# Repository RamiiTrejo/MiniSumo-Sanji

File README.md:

# MiniSumo-Sanji
Minisumo

 ## PLaca de Sanji
  Sanji contará con una placa hecha medida la cual puede ser alimentada con baterias de 2s-3s (LiPo), Con un microcontrolador ESP32 Embebido posee la capacidad de llevar 7 sensores, 5 de distancia y 2 de piso, con Divisores de tension en caso de trabajar con 5v, posee drivers TA6586 los cuales pueden llegar a soportar 5A de corriente pico por cada motor, tiene la opcion de agregar Pantalla Oled de 0.91 de Preferencia, ServoMotor para utilizarlo con Banderas, y Modulo de Inicio IR de Arsumo, 2 Botones de Manejo, 2 para poder cargar Programas al ESP32, y 3 Leds indicadores en caso de no querer utilizar un Display

<div align="center">
<br>
 <strong>FRONT VIEW</strong>
</div> 

<div align="center">
 <br>
 <strong>BACK VIEW</strong>
</div> 

 # 3D Sanji

cómo se aprecia en kas imágenes, Sanji Llevara de momento 4 sensores JS40F De arsumo, también poseerá 1 par de ruedas JS2622, 2 sensores de línea QRE1113, y de momento par de Motores pololu N20 de 500RPM

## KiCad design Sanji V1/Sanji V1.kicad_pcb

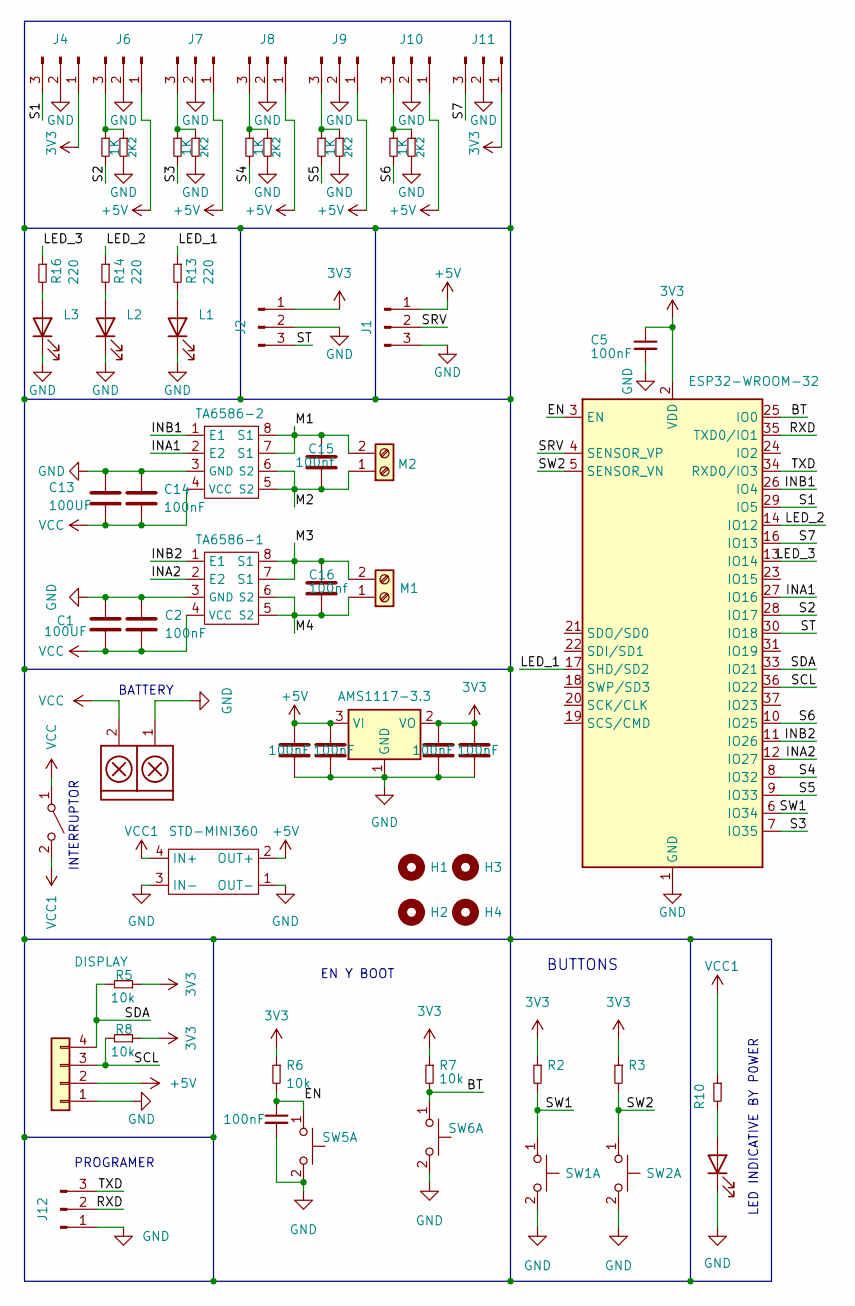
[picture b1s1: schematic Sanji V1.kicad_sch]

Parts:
Alimentacion1: TB_1X2; AMASS_XT30U-M_1x02_P5.0mm_Vertical
C1, C13: 100UF; CP_EIA-7343-20_Kemet-V
C2, C3, C4, C5, C6, C7, C8, C14: 100nF; C_0805_2012Metric_Pad1.18x1.45mm_HandSolder
C15, C16: 100nf; C_0805_2012Metric_Pad1.18x1.45mm_HandSolder
D2: LED; LED_0805_2012Metric_Pad1.15x1.40mm_HandSolder
H1, H2, H3, H4: MountingHole; MountingHole_3mm
J1, J2, J12: Conn_01x03_Pin; PinHeader_1x03_P2.54mm_Vertical
J3: DISPLAY; PinSocket_1x04_P2.54mm_Vertical
J4, J6, J7, J8, J9, J10, J11: Conn_01x03_Pin; PinHeader_1x03_P2.54mm_Horizontal
L1, L2, L3: LED; LED_0805_2012Metric_Pad1.15x1.40mm_HandSolder
M1: M1; JST_XH_S2B-XH-A-1_1x02_P2.50mm_Horizontal
M2: M2; JST_XH_S2B-XH-A-1_1x02_P2.50mm_Horizontal
R2, R3, R5, R6, R7, R8, R10: 10k; R_0805_2012Metric_Pad1.20x1.40mm_HandSolder
R13, R14, R16: 220; R_0805_2012Metric_Pad1.20x1.40mm_HandSolder
R15, R18, R20, R22, R24: 1K; R_0805_2012Metric_Pad1.20x1.40mm_HandSolder
R17, R19, R21, R23, R25: 2K2; R_0805_2012Metric_Pad1.20x1.40mm_HandSolder
STD-MINI360: STEP DOWN MINI 360
SW1, SW2, SW5, SW6: SW_Push_Dual_x2; SW_RS-032G05A3-SMRT
SWI1: SW_DPST_x2; PinHeader_1x03_P2.54mm_Vertical
TA6586-1, TA6586-2: DIP-8_W7.62mm
U1: AMS1117-3.3; SOT-223-3_TabPin2
U3: ESP32-WROOM-32

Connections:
3V3: C5.1, C7.1, C8.1, J2.1, J4.1, J11.1, R2.1, R3.1, R5.1, R6.1, R7.1, R8.1, U1.2 (VO), U3.2 (VDD)
+5V: C3.1, C4.1, J1.1, J3.2, J6.1, J7.1, J8.1, J9.1, J10.1, STD-MINI360.2 (OUT+), U1.3 (VI)
/BT: R7.2, SW6.1 (C), U3.25 (IO0)
/EN: C6.1, R6.2, SW5.1 (C), U3.3 (EN)
/INA1: TA6586-2.2 (E2), U3.27 (IO16)
/INA2: TA6586-1.2 (E2), U3.12 (IO27)
/INB1: TA6586-2.1 (E1), U3.26 (IO4)
/INB2: TA6586-1.1 (E1), U3.11 (IO26)
/LED_1: R13.1, U3.17 (SHD/SD2)
/LED_2: R14.1, U3.14 (IO12)
/LED_3: R16.1, U3.13 (IO14)
/M1: C15.1, M2.2, TA6586-2.7 (S1), TA6586-2.8 (S1)
/M2: C15.2, M2.1, TA6586-2.5 (S2), TA6586-2.6 (S2)
/M3: C16.1, M1.2, TA6586-1.7 (S1), TA6586-1.8 (S1)
/M4: C16.2, M1.1, TA6586-1.5 (S2), TA6586-1.6 (S2)
/RXD: J12.2, U3.35 (TXD0/IO1)
/S1: J4.3, U3.29 (IO5)
/S2: R15.2, U3.28 (IO17)
/S3: R18.2, U3.7 (IO35)
/S4: R20.2, U3.8 (IO32)
/S5: R22.2, U3.9 (IO33)
/S6: R24.2, U3.10 (IO25)
/S7: J11.3, U3.16 (IO13)
/SCL: J3.3, R8.2, U3.36 (IO22)
/SDA: J3.4, R5.2, U3.33 (IO21)
/SRV: J1.2, U3.4 (SENSOR_VP)
/ST: J2.3, U3.30 (IO18)
/SW1: R2.2, SW1.1 (C), U3.6 (IO34)
/SW2: R3.2, SW2.1 (C), U3.5 (SENSOR_VN)
/TXD: J12.3, U3.34 (RXD0/IO3)
GND: Alimentacion1.1, C1.1, C2.1, C3.2, C4.2, C5.2, C6.2, C7.2, C8.2, C13.1, C14.1, D2.1 (K), J1.3, J2.2, J3.1, J4.2, J6.2, J7.2, J8.2, J9.2, J10.2, J11.2, J12.1, L1.1 (K), L2.1 (K), L3.1 (K), R17.2, R19.2, R21.2, R23.2, R25.2, STD-MINI360.1 (OUT-), STD-MINI360.3 (IN-), SW1.2 (D), SW2.2 (D), SW5.2 (D), SW6.2 (D), TA6586-1.3 (GND), TA6586-2.3 (GND), U1.1 (GND), U3.1 (GND), U3.15 (GND), U3.38 (GND), U3.39 (GND)
unnamed: D2.2 (A), R10.2
unnamed: J6.3, R15.1, R17.1
unnamed: J7.3, R18.1, R19.1
unnamed: J8.3, R20.1, R21.1
unnamed: J9.3, R22.1, R23.1
unnamed: J10.3, R24.1, R25.1
unnamed: L1.2 (A), R13.2
unnamed: L2.2 (A), R14.2
unnamed: L3.2 (A), R16.2
VCC: Alimentacion1.2, C1.2, C2.2, C13.2, C14.2, SWI1.1 (A), TA6586-1.4 (VCC), TA6586-2.4 (VCC)
VCC1: R10.1, STD-MINI360.4 (IN+), SWI1.2 (B)

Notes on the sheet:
BUTTONS
EN Y BOOT
PROGRAMER
INTERRUPTOR
BATTERY
LED INDICATIVE BY P0WER

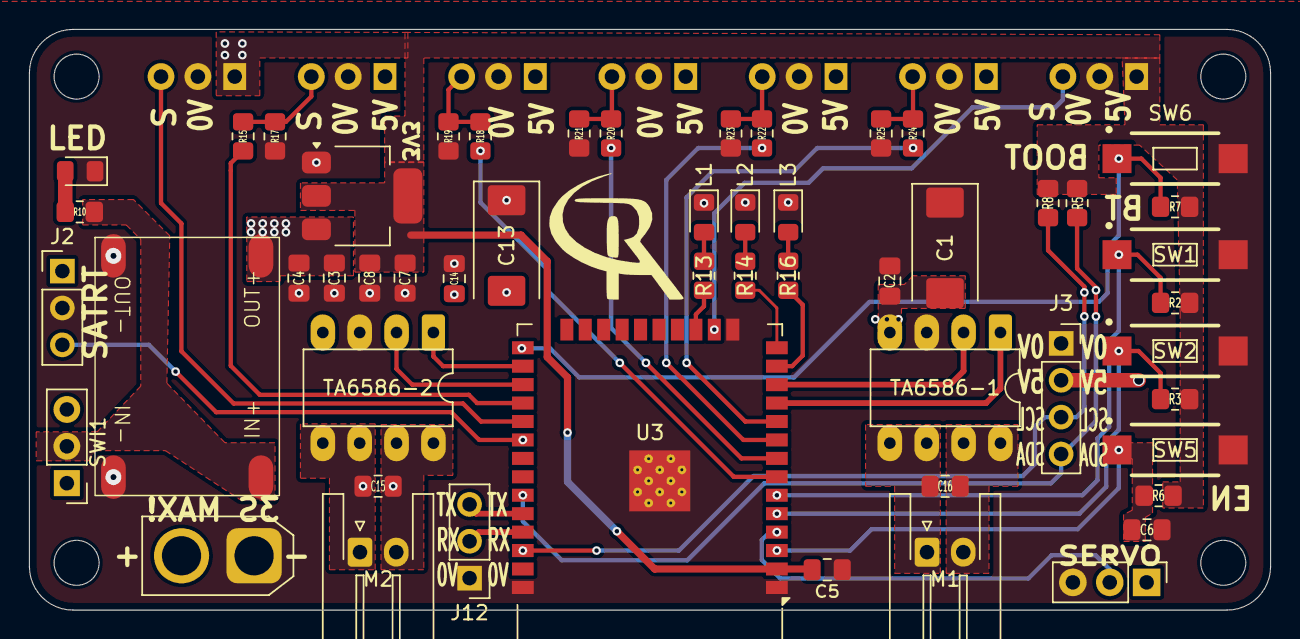
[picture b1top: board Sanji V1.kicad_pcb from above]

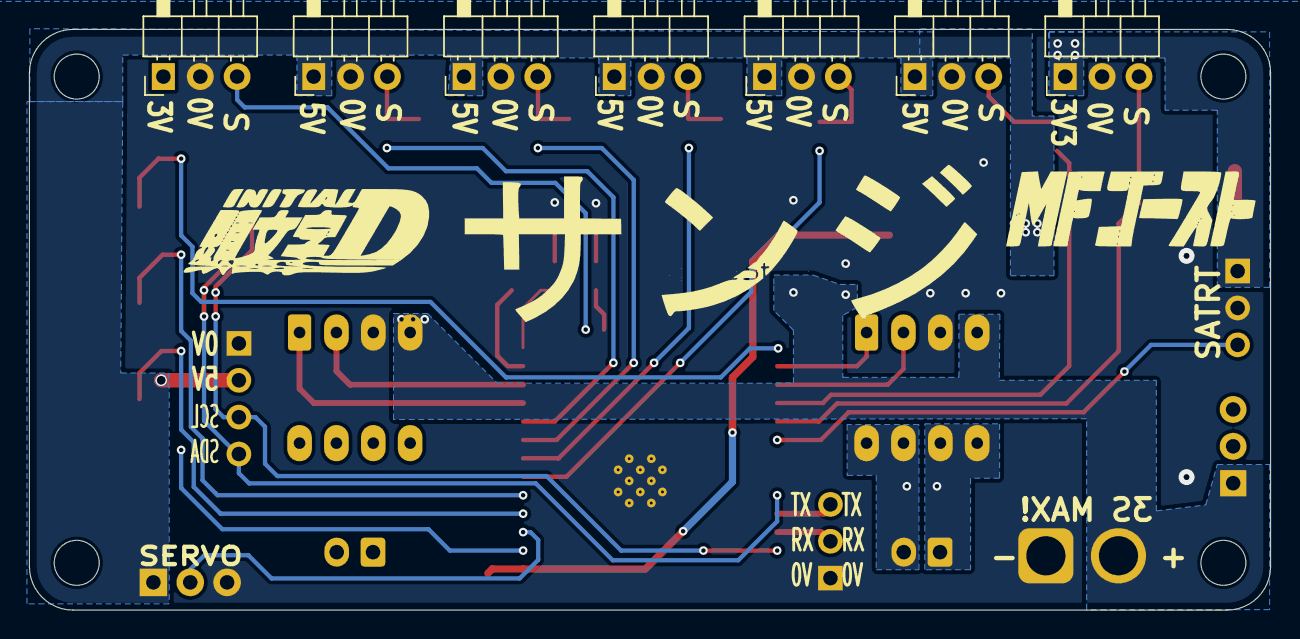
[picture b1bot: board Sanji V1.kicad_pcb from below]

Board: 2 copper layers, 85.5 x 40.0 mm, 64 parts (7 on the bottom side), 42 nets.

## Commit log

2026-01-17 Create 3D
